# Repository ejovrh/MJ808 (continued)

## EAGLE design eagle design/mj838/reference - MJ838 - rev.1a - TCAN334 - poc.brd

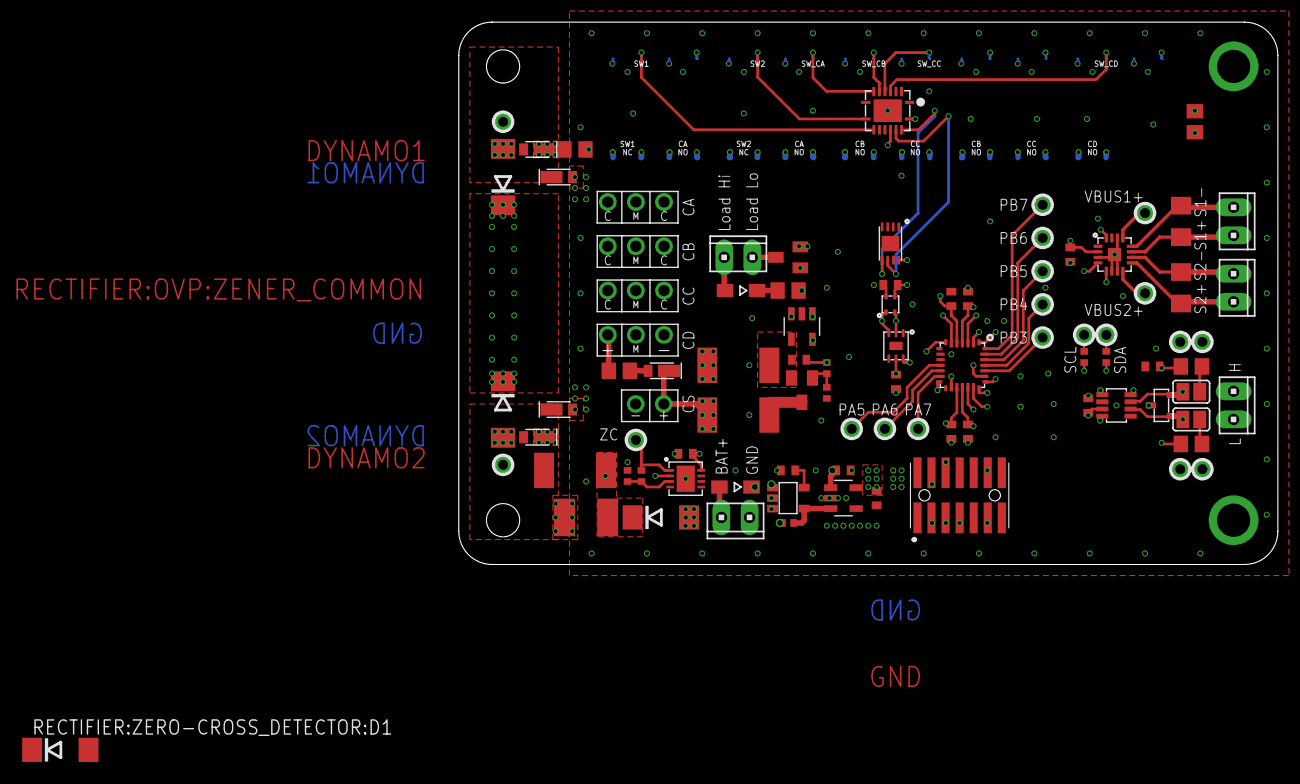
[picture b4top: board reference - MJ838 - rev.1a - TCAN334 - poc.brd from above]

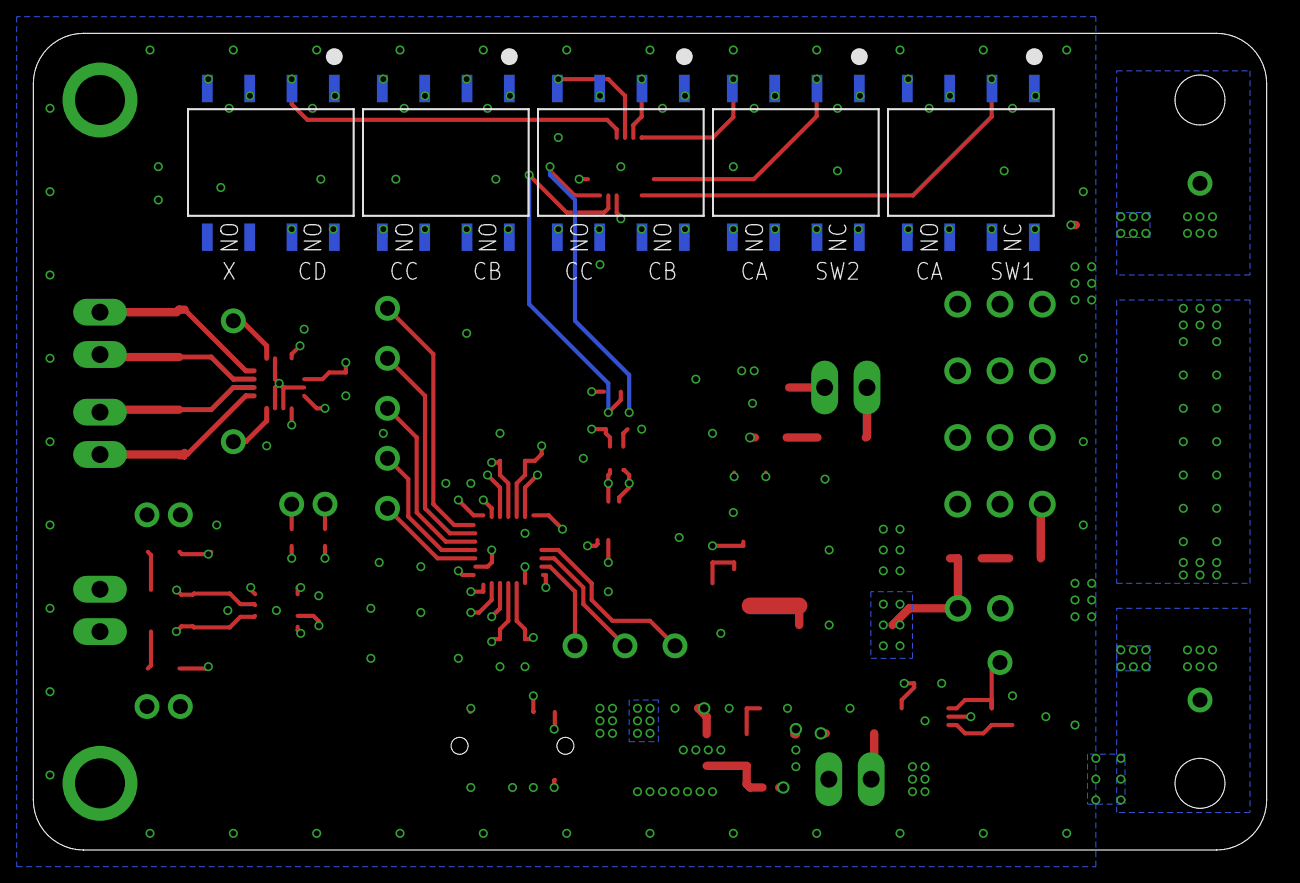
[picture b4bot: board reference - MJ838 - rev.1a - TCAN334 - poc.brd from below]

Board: 4 copper layers, 74.0 x 49.0 mm, 95 parts (5 on the bottom side), 68 nets.

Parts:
APP_LOAD:J3: Application; 10X02MTA
APP_LOAD:Q2: IRLML2402TRPBF; SOT23
C301, C305, C307, C405, C605, C801, C905: 0.1uF / 10V; C0402
C304: 1uF / 10V; C0402
C401: 47nF / 10V; C0402
C802: 0; C0402
D501, D502: BAT 60A E6327; SOD323-W
IC302: STM32F042G6U6; UFQFPN-28
IC401: TCAN334GDCNT; SOT23-8
IC402: SZNUP2105LT1G; SOT-23-3
IC602: PAC1952T-2E/4MX; VQFN16
IC701: MB85RC16PN-G-AMERE1; SON-8
IC801: DAC121C081CISD/NOPB; WSON-6
IC802: AD8515ARTZ-REEL7; SOT-23-5
IC901: SHT40-AD1F-R2; SMD
J1: Battery; 10X02MTA
J2: FTSH-107-01-L-DV-K-A; FTSH10701LDVKA
J3: CAN; 10X02MTA
J4: sense 1; 10X02MTA
J5: sense 2; 10X02MTA
Q802: IRLML2402TRPBF; SOT23
R1, R2: 4k7; R0402
R401, R402: 60R, 0.5W; R0805
R502, R504: 0R; R0805
R601, R602: 0.1R / 0.5W / 0.25%; R1206
R801: 12R/3W+++; R2512
R802: 0.1R / 1W; R2512
R803, R804: 0R; R0402
RECTIFIER:3V3:C1, RECTIFIER:3V3:C2, RECTIFIER:3V3:C7: 1uF / 10V; C0402
RECTIFIER:3V3:IC1: R3119N058A; SOT23-5
RECTIFIER:3V3:IC2: LDK320AM33R; SOT-23-5L
RECTIFIER:3V3:R1: 100k / 0.1W; R0402
RECTIFIER:GRAETZ+DELON:D1, RECTIFIER:GRAETZ+DELON:D2, RECTIFIER:GRAETZ+DELON:D3, RECTIFIER:GRAETZ+DELON:D4: CUHS20S30,H3F; US2H
RECTIFIER:GRAETZ+DELON:DELON:C1: 330μF / 35V / ultralow ESR; TH-2S
RECTIFIER:GRAETZ+DELON:DELON:SSR_NO/NO3:IC1: LAA710S; SMD_DIP8
RECTIFIER:GRAETZ+DELON:IC1: TLC59208FIRGYR; VQFN16
RECTIFIER:GRAETZ+DELON:R1: 430R/0.5W; R0805
RECTIFIER:GRAETZ+DELON:TUNING_CAPS:C2, RECTIFIER:GRAETZ+DELON:TUNING_CAPS:C3, RECTIFIER:GRAETZ+DELON:TUNING_CAPS:C4: 1500μF / 35V / ultralow ESR; TH-2S-BACK-TO-BACK
RECTIFIER:GRAETZ+DELON:TUNING_CAPS:R2: 47k; R0805
RECTIFIER:GRAETZ+DELON:TUNING_CAPS:SSR_NC/NO1:IC2, RECTIFIER:GRAETZ+DELON:TUNING_CAPS:SSR_NC/NO2:IC2: LBA710S; SMD_DIP8
RECTIFIER:GRAETZ+DELON:TUNING_CAPS:SSR_NO/NO1:IC1, RECTIFIER:GRAETZ+DELON:TUNING_CAPS:SSR_NO/NO2:IC1: LAA710S; SMD_DIP8
RECTIFIER:OVP:D1, RECTIFIER:OVP:D2: 19V/5W; DO214AA
RECTIFIER:SMOOTHING_CAP:C5: 2P 4700μF / 35V / ultralow ESR; TH
RECTIFIER:SMOOTHING_CAP:D8: CUHS20S30,H3F; US2H
RECTIFIER:ZERO-CROSS_DETECTOR:C3: 0.1uF / 10V; C0402
RECTIFIER:ZERO-CROSS_DETECTOR:C8: 10nF / 100v; C1812
RECTIFIER:ZERO-CROSS_DETECTOR:D1, RECTIFIER:ZERO-CROSS_DETECTOR:D10: 6V/3W; DO214AA
RECTIFIER:ZERO-CROSS_DETECTOR:IC1: LT1638IDD#PBF; DFN-8
RECTIFIER:ZERO-CROSS_DETECTOR:R1: 10k/3W; R2512
RECTIFIER:ZERO-CROSS_DETECTOR:R2, RECTIFIER:ZERO-CROSS_DETECTOR:R7: 10k; R0402
SJ401: CAN H term.; SJ
SJ402: CAN L term.; SJ
TP2, TP3, TP4, TP5, TP6, TP7, TP8, TP10, TP11, TP12, TP16, TP17, TP22, TP23, TP24, TP25: CAN high; TH-0.9
TP18, TP19: CAN low; TH-0.9
TP31: BAT+; TH-0.9

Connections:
3V3: C301.2, C304.2, C305.2, C405.1, C605.1, C801.2, C905.1, IC302.5_VDDA, IC302.17_VDD, IC302.18_VDDIO2, IC401.P$3, IC602.2, IC701.P$8, IC801.5, IC802.5, IC901.VDD, J2.3, R1.2, R2.2, RECTIFIER:3V3:C7.2, RECTIFIER:3V3:IC2.OUT, RECTIFIER:GRAETZ+DELON:IC1.16, RECTIFIER:GRAETZ+DELON:R1.2, RECTIFIER:ZERO-CROSS_DETECTOR:C3.2, RECTIFIER:ZERO-CROSS_DETECTOR:IC1.8_V+
12R_OHMIC_LOAD:DAC_OUT: IC801.6, IC802.3
12R_OHMIC_LOAD:GATE1: Q802.1, R803.2, R804.1
12R_OHMIC_LOAD:LOAD_LOW: Q802.3, R801.1
12R_OHMIC_LOAD:OPAMP_OUT: C802.2, IC802.1, R803.1
12R_OHMIC_LOAD:VSENSE: C802.1, IC802.4, Q802.2, R802.2
!APP_LOAD!: APP_LOAD:Q2.1, IC302.7_PA1
!LED_RST!: IC302.6_PA0, RECTIFIER:GRAETZ+DELON:IC1.13
!STBY!: IC302.23_PA15, IC401.P$8
APP_LOAD:LOAD_LOW: APP_LOAD:J3.1, APP_LOAD:Q2.3
BAT+: D501.A, J1.1
CAN_H: IC401.P$7, IC402.2, J3.2, SJ401.1, TP16.P$1, TP17.P$1
CAN_INFRA:H: R402.2, SJ401.2
CAN_INFRA:L: R401.1, SJ402.2
CAN_INFRA:SPLIT: C401.1, R401.2, R402.1
CAN_L: IC401.P$6, IC402.1, J3.1, SJ402.1, TP18.P$1, TP19.P$1
CAN_RX: IC302.19_PA9-[PA11], IC401.P$4
CAN_TX: IC302.20_PA10-[PA12], IC401.P$1
DYNAMO1: RECTIFIER:GRAETZ+DELON:D1.C, RECTIFIER:GRAETZ+DELON:D2.A, RECTIFIER:GRAETZ+DELON:TUNING_CAPS:SSR_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.6_DRAIN2-2, RECTIFIER:GRAETZ+DELON:TUNING_CAPS:SSR_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.8_DRAIN1-2, RECTIFIER:GRAETZ+DELON:TUNING_CAPS:SSR_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.6_DRAIN2-2, RECTIFIER:GRAETZ+DELON:TUNING_CAPS:SSR_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.8_DRAIN1-2, RECTIFIER:OVP:D1.A, TP2.P$1
DYNAMO2: RECTIFIER:GRAETZ+DELON:D3.C, RECTIFIER:GRAETZ+DELON:D4.A, RECTIFIER:GRAETZ+DELON:TUNING_CAPS:SSR_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.7_DRAIN1-1, RECTIFIER:OVP:D2.A, RECTIFIER:ZERO-CROSS_DETECTOR:R1.1, TP3.P$1
GND: APP_LOAD:Q2.2, C301.1, C304.1, C305.1, C307.1, C401.2, C405.2, C605.2, C801.1, C905.2, IC302.16_VSS, IC401.P$2, IC402.3, IC602.3, IC602.6, IC602.7, IC602.14, IC602.17, IC701.P$1, IC701.P$2, IC701.P$3, IC701.P$4, IC701.P$9, IC801.1, IC801.4, IC801.7, IC802.2, IC901.VSS, J1.2, J2.5, J2.7, J2.11, R802.1, R804.2, RECTIFIER:3V3:C1.2, RECTIFIER:3V3:C2.2, RECTIFIER:3V3:C7.1, RECTIFIER:3V3:IC1.2_GND, RECTIFIER:3V3:IC1.3_GND, RECTIFIER:3V3:IC2.GND, RECTIFIER:GRAETZ+DELON:D2.C, RECTIFIER:GRAETZ+DELON:D4.C, RECTIFIER:GRAETZ+DELON:DELON:C1.3_NEG, RECTIFIER:GRAETZ+DELON:IC1.1, RECTIFIER:GRAETZ+DELON:IC1.2, RECTIFIER:GRAETZ+DELON:IC1.3, RECTIFIER:GRAETZ+DELON:IC1.8, RECTIFIER:GRAETZ+DELON:IC1.17, RECTIFIER:SMOOTHING_CAP:C5.NEG, RECTIFIER:ZERO-CROSS_DETECTOR:C3.1, RECTIFIER:ZERO-CROSS_DETECTOR:C8.1, RECTIFIER:ZERO-CROSS_DETECTOR:D10.A, RECTIFIER:ZERO-CROSS_DETECTOR:IC1.4_V-, RECTIFIER:ZERO-CROSS_DETECTOR:IC1.9_V-, RECTIFIER:ZERO-CROSS_DETECTOR:R2.1
I2C_SCL: IC302.3_PF1, IC602.4, IC701.P$6, IC801.2, IC901.SCL, R1.1, RECTIFIER:GRAETZ+DELON:IC1.14, TP22.P$1
I2C_SDA: IC302.2_PF0, IC602.5, IC701.P$5, IC801.3, IC901.SDA, R2.1, RECTIFIER:GRAETZ+DELON:IC1.15, TP23.P$1
PA5: IC302.11_PA5, TP12.P$1
PA6: IC302.12_PA6, TP11.P$1
PA7: IC302.13_PA7, TP10.P$1
PB3: IC302.24_PB3, TP4.P$1
PB4: IC302.25_PB4, TP5.P$1
PB5: IC302.26_PB5, TP6.P$1
PB6: IC302.27_PB6, TP7.P$1
PB7: IC302.28_PB7, TP8.P$1
PM_!PWRDN!: IC302.1_PB8, IC602.16
RECTIFIER:3V3:!EN!: RECTIFIER:3V3:IC1.4_DOUT, RECTIFIER:3V3:IC2.EN, RECTIFIER:3V3:R1.2
RECTIFIER:3V3:CD: RECTIFIER:3V3:C1.1, RECTIFIER:3V3:IC1.5_CD
RECTIFIER:GRAETZ+DELON:!SW1!: RECTIFIER:GRAETZ+DELON:IC1.10, RECTIFIER:GRAETZ+DELON:TUNING_CAPS:SSR_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.2_CATHODE1
RECTIFIER:GRAETZ+DELON:!SW2!: RECTIFIER:GRAETZ+DELON:IC1.9, RECTIFIER:GRAETZ+DELON:TUNING_CAPS:SSR_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.2_CATHODE1
RECTIFIER:GRAETZ+DELON:!SW_CA!: RECTIFIER:GRAETZ+DELON:IC1.7, RECTIFIER:GRAETZ+DELON:TUNING_CAPS:SSR_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.4_CATHODE2, RECTIFIER:GRAETZ+DELON:TUNING_CAPS:SSR_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.4_CATHODE2
RECTIFIER:GRAETZ+DELON:!SW_CB!: RECTIFIER:GRAETZ+DELON:IC1.6, RECTIFIER:GRAETZ+DELON:TUNING_CAPS:SSR_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.2_CATHODE1, RECTIFIER:GRAETZ+DELON:TUNING_CAPS:SSR_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.2_CATHODE1
RECTIFIER:GRAETZ+DELON:!SW_CC!: RECTIFIER:GRAETZ+DELON:IC1.5, RECTIFIER:GRAETZ+DELON:TUNING_CAPS:SSR_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.4_CATHODE2, RECTIFIER:GRAETZ+DELON:TUNING_CAPS:SSR_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.4_CATHODE2
RECTIFIER:GRAETZ+DELON:!SW_CD!: RECTIFIER:GRAETZ+DELON:DELON:SSR_NO/NO3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.2_CATHODE1, RECTIFIER:GRAETZ+DELON:IC1.4
RECTIFIER:GRAETZ+DELON:DELON: RECTIFIER:GRAETZ+DELON:DELON:SSR_NO/NO3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.8_DRAIN1-2, RECTIFIER:GRAETZ+DELON:TUNING_CAPS:SSR_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.7_DRAIN1-1, RECTIFIER:GRAETZ+DELON:TUNING_CAPS:SSR_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.6_DRAIN2-2, RECTIFIER:GRAETZ+DELON:TUNING_CAPS:SSR_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.8_DRAIN1-2, RECTIFIER:GRAETZ+DELON:TUNING_CAPS:SSR_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.6_DRAIN2-2, RECTIFIER:GRAETZ+DELON:TUNING_CAPS:SSR_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.8_DRAIN1-2
RECTIFIER:GRAETZ+DELON:DELON:SW1_OUT: RECTIFIER:GRAETZ+DELON:DELON:C1.2_MID, RECTIFIER:GRAETZ+DELON:DELON:SSR_NO/NO3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.7_DRAIN1-1
RECTIFIER:GRAETZ+DELON:SSR_ANODE: RECTIFIER:GRAETZ+DELON:DELON:SSR_NO/NO3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.1_ANODE1, RECTIFIER:GRAETZ+DELON:DELON:SSR_NO/NO3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.3_ANODE2, RECTIFIER:GRAETZ+DELON:R1.1, RECTIFIER:GRAETZ+DELON:TUNING_CAPS:SSR_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.1_ANODE1, RECTIFIER:GRAETZ+DELON:TUNING_CAPS:SSR_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.3_ANODE2, RECTIFIER:GRAETZ+DELON:TUNING_CAPS:SSR_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.1_ANODE1, RECTIFIER:GRAETZ+DELON:TUNING_CAPS:SSR_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.3_ANODE2, RECTIFIER:GRAETZ+DELON:TUNING_CAPS:SSR_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.1_ANODE1, RECTIFIER:GRAETZ+DELON:TUNING_CAPS:SSR_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.3_ANODE2, RECTIFIER:GRAETZ+DELON:TUNING_CAPS:SSR_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.1_ANODE1, RECTIFIER:GRAETZ+DELON:TUNING_CAPS:SSR_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.3_ANODE2
RECTIFIER:GRAETZ+DELON:TUNING_CAPS:CAA: RECTIFIER:GRAETZ+DELON:TUNING_CAPS:C2.1_C, RECTIFIER:GRAETZ+DELON:TUNING_CAPS:SSR_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.5_DRAIN2-1
RECTIFIER:GRAETZ+DELON:TUNING_CAPS:CAB: RECTIFIER:GRAETZ+DELON:TUNING_CAPS:C2.3_C, RECTIFIER:GRAETZ+DELON:TUNING_CAPS:SSR_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.5_DRAIN2-1
RECTIFIER:GRAETZ+DELON:TUNING_CAPS:CBA: RECTIFIER:GRAETZ+DELON:TUNING_CAPS:C3.1_C, RECTIFIER:GRAETZ+DELON:TUNING_CAPS:SSR_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.7_DRAIN1-1
RECTIFIER:GRAETZ+DELON:TUNING_CAPS:CBB: RECTIFIER:GRAETZ+DELON:TUNING_CAPS:C3.3_C, RECTIFIER:GRAETZ+DELON:TUNING_CAPS:SSR_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.7_DRAIN1-1
RECTIFIER:GRAETZ+DELON:TUNING_CAPS:CCA: RECTIFIER:GRAETZ+DELON:TUNING_CAPS:C4.1_C, RECTIFIER:GRAETZ+DELON:TUNING_CAPS:SSR_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.5_DRAIN2-1
RECTIFIER:GRAETZ+DELON:TUNING_CAPS:CCB: RECTIFIER:GRAETZ+DELON:TUNING_CAPS:C4.3_C, RECTIFIER:GRAETZ+DELON:TUNING_CAPS:SSR_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.5_DRAIN2-1
RECTIFIER:GRAETZ+DELON:TUNING_CAPS:TUNING_CAP_BIAS: RECTIFIER:GRAETZ+DELON:TUNING_CAPS:C2.2_MID, RECTIFIER:GRAETZ+DELON:TUNING_CAPS:C3.2_MID, RECTIFIER:GRAETZ+DELON:TUNING_CAPS:C4.2_MID, RECTIFIER:GRAETZ+DELON:TUNING_CAPS:R2.1
RECTIFIER:LDO_IN: D501.C, R504.2, RECTIFIER:3V3:C2.1, RECTIFIER:3V3:IC1.1_VDD, RECTIFIER:3V3:IC2.IN, RECTIFIER:3V3:R1.1
RECTIFIER:OVP:ZENER_COMMON: RECTIFIER:OVP:D1.C, RECTIFIER:OVP:D2.C
RECTIFIER:SMOOTHINGCAP_IN: R502.2, RECTIFIER:SMOOTHING_CAP:D8.C
RECTIFIER:VDC_TOWARDS_LDO: D502.C, R504.1
RECTIFIER:V_RECT_TP1-IN: R502.1, RECTIFIER:GRAETZ+DELON:D1.A, RECTIFIER:GRAETZ+DELON:D3.A, RECTIFIER:GRAETZ+DELON:DELON:C1.1_POS, RECTIFIER:GRAETZ+DELON:TUNING_CAPS:R2.2
RECTIFIER:ZERO-CROSS_DETECTOR:OPAMP_IN+: RECTIFIER:ZERO-CROSS_DETECTOR:IC1.3_A_IN+, RECTIFIER:ZERO-CROSS_DETECTOR:R2.2, RECTIFIER:ZERO-CROSS_DETECTOR:R7.2
RECTIFIER:ZERO-CROSS_DETECTOR:OPAMP_IN-: RECTIFIER:ZERO-CROSS_DETECTOR:C8.2, RECTIFIER:ZERO-CROSS_DETECTOR:D10.C, RECTIFIER:ZERO-CROSS_DETECTOR:IC1.2_A_IN-, RECTIFIER:ZERO-CROSS_DETECTOR:R1.2
SENSE1+: IC602.11, J4.1, R601.1
SENSE1-: IC602.12, J4.2, R601.2
SENSE2+: IC602.10, J5.2, R602.1
SENSE2-: IC602.9, J5.1, R602.2
SYS_NRST: C307.2, IC302.4_NRST, J2.12
SYS_SWCLK: IC302.22_PA14, J2.6
SYS_SWDIO: IC302.21_PA13, J2.4
VBUS1+: IC602.13, TP24.P$1
VBUS2+: IC602.8, TP25.P$1
VDC: APP_LOAD:J3.2, D502.A, R801.2, RECTIFIER:SMOOTHING_CAP:C5.POS, RECTIFIER:SMOOTHING_CAP:D8.A
ZEROCROSS: IC302.14_PB0, RECTIFIER:ZERO-CROSS_DETECTOR:IC1.1_A_OUT, RECTIFIER:ZERO-CROSS_DETECTOR:R7.1, TP31.P$1

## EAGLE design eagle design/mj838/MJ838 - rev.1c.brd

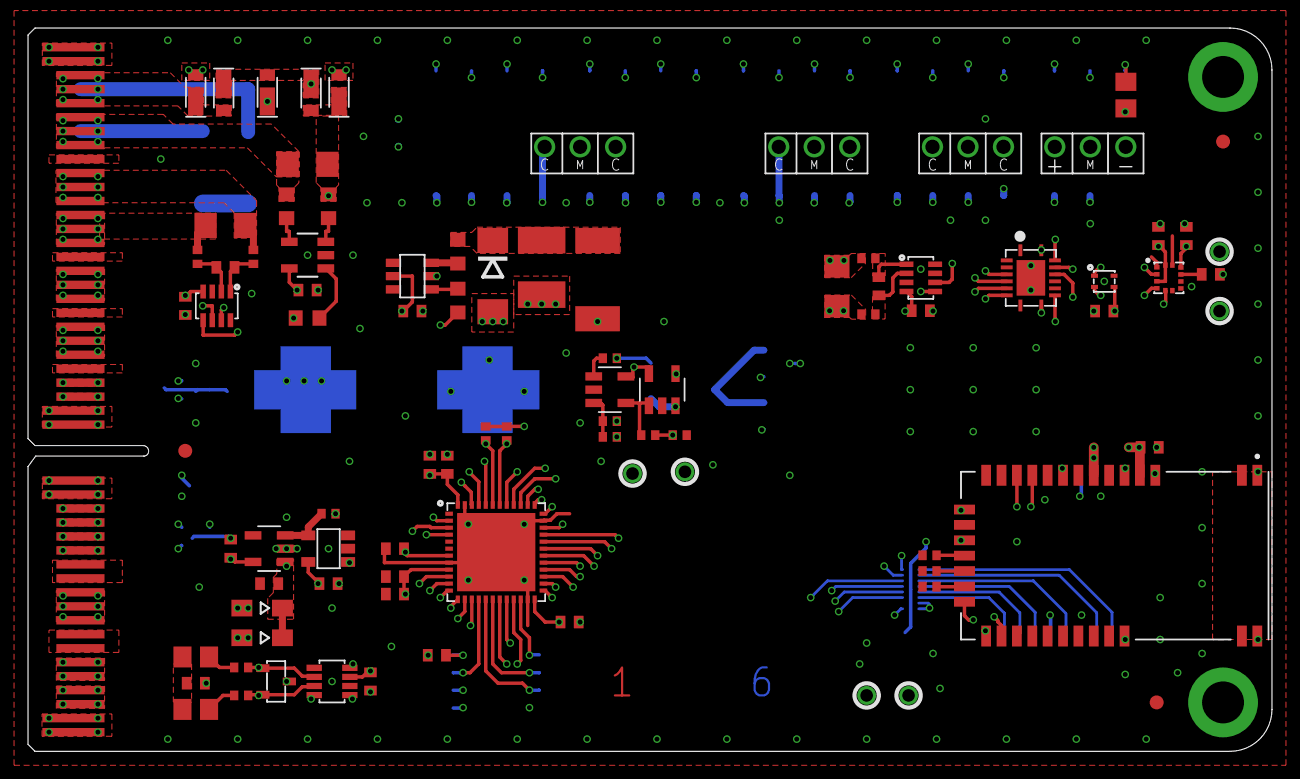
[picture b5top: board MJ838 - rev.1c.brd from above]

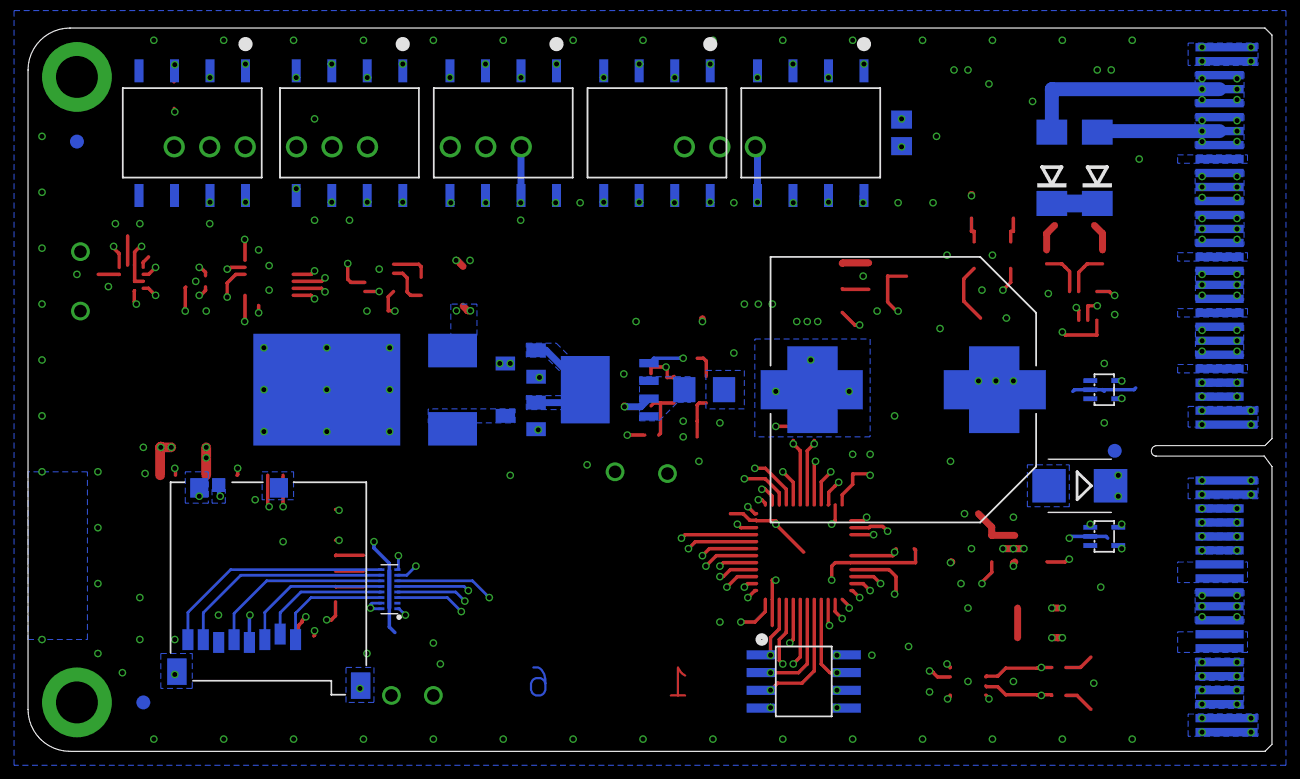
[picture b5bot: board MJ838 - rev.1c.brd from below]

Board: 6 copper layers, 89.0 x 51.8 mm, 114 parts (24 on the bottom side), 102 nets.

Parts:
ACCELEROMETER:C1: 0.1uF / 10V; C0402
ACCELEROMETER:C2: 0.2uF / 10V; C0402
ACCELEROMETER:C4: 0.11uF / 10V; C0402
ACCELEROMETER:IC1: ADXL367BCCZ-RL7; LGA-12
ADJUSTABLE_LOAD:IC2, ADJUSTABLE_LOAD:IC4: AD8515ARTZ-REEL7; SOT-23-5
ADJUSTABLE_LOAD:IC3: PH2925U,115; SOT669
ADJUSTABLE_LOAD:INA219:C1: 0.1uF / 10V; C0402
ADJUSTABLE_LOAD:INA219:C2: ???; C0402
ADJUSTABLE_LOAD:INA219:IC3: INA219BIDCNT; SOT-23-8
ADJUSTABLE_LOAD:INA219:R3, ADJUSTABLE_LOAD:INA219:R5: ???; R0402
ADJUSTABLE_LOAD:INA219:R4: 0.1R / 0.5W - LVK12R100CER; R1206
ADJUSTABLE_LOAD:Q2, ADJUSTABLE_LOAD:Q3: BSS123; SOT23
ADJUSTABLE_LOAD:R1: 3k; R0402
ADJUSTABLE_LOAD:R2: 0.1R / 0.5W - LVK12R100CER; R1206
ADJUSTABLE_LOAD:R3: 1k; R0402
ADJUSTABLE_LOAD:R4: 27k; R0402
ADJUSTABLE_LOAD:R5: 12R, 20W, AP725 12R F; TO-263-2
ADJUSTABLE_LOAD:R6: 100k; R0402
ADJUSTABLE_LOAD:R7: 10k; R0402
BLUETOOTH:C1: 10uF / 10V; C0402
BLUETOOTH:IC1: RN4678-V/RM113; MODULE_RN4678-V/RM100
BLUETOOTH:R1, BLUETOOTH:R2, BLUETOOTH:R3: 0R; R0402
CAN_INFRA:C1: 47nF / 10V; C0402
CAN_INFRA:C5: 0.1uF / 10V; C0402
CAN_INFRA:IC1: TCAN334GDCNT; SOT23-8
CAN_INFRA:IC2: SZNUP2105LT1G; SOT-23-3
CAN_INFRA:R1, CAN_INFRA:R2: 60R, 0.5W; R0805
CAN_INFRA:R3, CAN_INFRA:R4: 0; R0402
CONN1: MEC1-150-02-F-D-RA1-SL; SMD
D1: SMLVT3V3; SMB
FID1, FID2, FID3, FID4, FID5, FID6: n/a; FIDUCIAL_1MM
HUMIDITY_SENSOR:C5: 0.1uF / 10V; C0402
HUMIDITY_SENSOR:IC1: SHT40-AD1F-R2; SMD
IC1, IC2: ESDALC6V1W5; SOT323-5
INA1:C1: 0.1uF / 10V; C0402
INA1:C2: ???; C0402
INA1:IC3: INA219BIDCNT; SOT-23-8
INA1:R3, INA1:R5: ???; R0402
INA1:R4: 0.1R / 0.5W - LVK12R100CER; R1206
M-RAM:C2: 0.1uF / 10V; C0402
M-RAM:IC1: S3A3204V0M-AI1AT; SOIC08
MARKER1: 6 layer; 6L
RECTIFIER:3V3:C1, RECTIFIER:3V3:C2, RECTIFIER:3V3:C7: 1uF / 10V; C0402
RECTIFIER:3V3:IC1: R3119N058A; SOT23-5
RECTIFIER:3V3:IC2: LDK320AM33R; SOT-23-5L
RECTIFIER:3V3:R1: 100k / 0.1W; R0402
RECTIFIER:D1, RECTIFIER:D2: BAT 60A E6327; SOD323-W
RECTIFIER:DYNAMO_OVP:D3, RECTIFIER:DYNAMO_OVP:D4: 19V/5W; DO214AA
RECTIFIER:GRAETZ+DELON:D1, RECTIFIER:GRAETZ+DELON:D2, RECTIFIER:GRAETZ+DELON:D3, RECTIFIER:GRAETZ+DELON:D4: CUHS20S30,H3F; US2H
RECTIFIER:GRAETZ+DELON:DELON:C1: 330μF / 35V / ultralow ESR; TH-2S
RECTIFIER:GRAETZ+DELON:DELON:SSR_NO/NO3:IC1: LAA710S; SMD_DIP8
RECTIFIER:GRAETZ+DELON:IC1: TLC59208FIRGYR; VQFN16
RECTIFIER:GRAETZ+DELON:R1: 625; R0805
RECTIFIER:GRAETZ+DELON:TUNING_CAPS:C2, RECTIFIER:GRAETZ+DELON:TUNING_CAPS:C3, RECTIFIER:GRAETZ+DELON:TUNING_CAPS:C4: 1500μF / 35V / ultralow ESR; TH-2S-BACK-TO-BACK
RECTIFIER:GRAETZ+DELON:TUNING_CAPS:R2: 47k; R0805
RECTIFIER:GRAETZ+DELON:TUNING_CAPS:SSR_NO/NO1:IC1, RECTIFIER:GRAETZ+DELON:TUNING_CAPS:SSR_NO/NO2:IC1, RECTIFIER:GRAETZ+DELON:TUNING_CAPS:SSR_NO/NO3:IC1, RECTIFIER:GRAETZ+DELON:TUNING_CAPS:SSR_NO/NO4:IC1: LAA710S; SMD_DIP8
RECTIFIER:PHASE_SHIFT:C1: 0.1uF / 10V; C0402
RECTIFIER:PHASE_SHIFT:IC1: LT1716CS5#TRMPBF; SOT23-5
RECTIFIER:PHASE_SHIFT:R1, RECTIFIER:PHASE_SHIFT:R2, RECTIFIER:PHASE_SHIFT:R3: 0R; R0603
RECTIFIER:PHASE_SHIFT:R4: 0.01R / 0.5W / 0.25%; R1206
RECTIFIER:SMOOTHING_CAP:C1: EEE-FK1E472SV; CAP_EEEFK1E472SV
RECTIFIER:SMOOTHING_CAP:D8: CUHS20S30,H3F; US2H
RECTIFIER:ZERO-CROSS_DETECTOR:C3: 0.1uF / 10V; C0402
RECTIFIER:ZERO-CROSS_DETECTOR:C8: 10nF / 100v; C1812
RECTIFIER:ZERO-CROSS_DETECTOR:D1: 6V/3W; DO214AA
RECTIFIER:ZERO-CROSS_DETECTOR:IC1: TLV6703DDCR; SOT-23
RECTIFIER:ZERO-CROSS_DETECTOR:R1: 10k/3W; R2512
RECTIFIER:ZERO-CROSS_DETECTOR:R2, RECTIFIER:ZERO-CROSS_DETECTOR:R3: 0R; R0603
SD_CARD:IC1: 0473521001; SMD
SD_CARD:IC3: EMIF06-MSD02N16; MICRO_QFN
STM32L4:C1, STM32L4:C2, STM32L4:C4, STM32L4:C8: 0.1uF / 10V; C0402
STM32L4:C3: 4.7uF / 10V; C0402
STM32L4:C6: 1uF / 10V; C0402
STM32L4:IC1: STM32L4P5CGU6; UFQFPN48
STM32L4:R1, STM32L4:R2: 1k; R0402
TP1, TP2, TP3, TP4, TP5, TP6: CAN high; TH-0.9

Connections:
3V3: ACCELEROMETER:C1.2, ACCELEROMETER:C4.2, ACCELEROMETER:IC1.3_MISO/ASEL, ACCELEROMETER:IC1.10_VS, ACCELEROMETER:IC1.12_VDDIO, ADJUSTABLE_LOAD:IC2.5, ADJUSTABLE_LOAD:IC4.5, ADJUSTABLE_LOAD:INA219:C1.1, ADJUSTABLE_LOAD:INA219:IC3.P$4, ADJUSTABLE_LOAD:R6.2, BLUETOOTH:C1.2, BLUETOOTH:IC1.4, BLUETOOTH:IC1.7, CAN_INFRA:C5.1, CAN_INFRA:IC1.P$3, CONN1.33, CONN1.34, D1.C, HUMIDITY_SENSOR:C5.1, HUMIDITY_SENSOR:IC1.VDD, INA1:C1.1, INA1:IC3.P$4, INA1:IC3.P$7, M-RAM:C2.2, M-RAM:IC1.8, RECTIFIER:3V3:C7.2, RECTIFIER:3V3:IC2.OUT, RECTIFIER:GRAETZ+DELON:IC1.16, RECTIFIER:GRAETZ+DELON:R1.2, RECTIFIER:PHASE_SHIFT:C1.2, RECTIFIER:PHASE_SHIFT:IC1.5, RECTIFIER:ZERO-CROSS_DETECTOR:C3.2, RECTIFIER:ZERO-CROSS_DETECTOR:IC1.P$5, SD_CARD:IC1.VDD, SD_CARD:IC3.15, SD_CARD:IC3.16, STM32L4:C1.2, STM32L4:C2.2, STM32L4:C3.2, STM32L4:C6.2, STM32L4:C8.2, STM32L4:IC1.P$9, STM32L4:IC1.P$24, STM32L4:IC1.P$48, STM32L4:R1.2, STM32L4:R2.2
!LED_RST!: RECTIFIER:GRAETZ+DELON:IC1.13, STM32L4:IC1.P$44
!QSPI_CS!: M-RAM:IC1.1, STM32L4:IC1.P$22
!RN4678_SWBTN!: BLUETOOTH:IC1.5, STM32L4:IC1.P$2
!STBY!: CAN_INFRA:IC1.P$8, STM32L4:IC1.P$13
ACCELEROMETER:VREG: ACCELEROMETER:C2.2, ACCELEROMETER:IC1.9_VREG_OUT
ADJL: ADJUSTABLE_LOAD:Q2.1, STM32L4:IC1.P$38
ADJUSTABLE_LOAD:DRAIN: ADJUSTABLE_LOAD:IC3.D, ADJUSTABLE_LOAD:Q2.2, ADJUSTABLE_LOAD:Q3.2
ADJUSTABLE_LOAD:GATE_COMMON: ADJUSTABLE_LOAD:IC3.G, ADJUSTABLE_LOAD:R3.2
ADJUSTABLE_LOAD:GATE_COMMON-DRIVER_OUT: ADJUSTABLE_LOAD:IC2.1, ADJUSTABLE_LOAD:R3.1
ADJUSTABLE_LOAD:IN+: ADJUSTABLE_LOAD:IC2.3, ADJUSTABLE_LOAD:R6.1, ADJUSTABLE_LOAD:R7.2
ADJUSTABLE_LOAD:IN-: ADJUSTABLE_LOAD:INA219:R3.2, ADJUSTABLE_LOAD:INA219:R4.2, ADJUSTABLE_LOAD:R5.2
ADJUSTABLE_LOAD:INA219:IN+L: ADJUSTABLE_LOAD:INA219:C2.1, ADJUSTABLE_LOAD:INA219:IC3.P$1, ADJUSTABLE_LOAD:INA219:R5.1
ADJUSTABLE_LOAD:INA219:IN-H: ADJUSTABLE_LOAD:INA219:C2.2, ADJUSTABLE_LOAD:INA219:IC3.P$2, ADJUSTABLE_LOAD:INA219:R3.1
ADJUSTABLE_LOAD:LOAD_LOW: ADJUSTABLE_LOAD:Q2.3, ADJUSTABLE_LOAD:R5.1
ADJUSTABLE_LOAD:SENSE_AMP_IN-: ADJUSTABLE_LOAD:IC4.4, ADJUSTABLE_LOAD:R1.2, ADJUSTABLE_LOAD:R4.1
ADJUSTABLE_LOAD:VSENSE: ADJUSTABLE_LOAD:IC3.S1, ADJUSTABLE_LOAD:IC3.S2, ADJUSTABLE_LOAD:IC3.S3, ADJUSTABLE_LOAD:IC4.3, ADJUSTABLE_LOAD:R2.2
ADJUSTABLE_LOAD:VSENSE-AMP_OUT: ADJUSTABLE_LOAD:IC2.4, ADJUSTABLE_LOAD:IC4.1, ADJUSTABLE_LOAD:R4.2
ADXL_INT1: ACCELEROMETER:IC1.5_INT1, STM32L4:IC1.P$15
APPL: ADJUSTABLE_LOAD:Q3.1, STM32L4:IC1.P$29
APP_LOW: ADJUSTABLE_LOAD:Q3.3, CONN1.55, CONN1.56, CONN1.57, CONN1.58, CONN1.59, CONN1.60
BAT+: CONN1.17, CONN1.18, CONN1.19, CONN1.20, CONN1.21, CONN1.22, RECTIFIER:D1.A
BLUETOOTH:EAN: BLUETOOTH:IC1.20, BLUETOOTH:R3.1
BLUETOOTH:P2_0: BLUETOOTH:IC1.18, BLUETOOTH:R1.1
BLUETOOTH:P2_4: BLUETOOTH:IC1.19, BLUETOOTH:R2.1
CAN_H: CAN_INFRA:IC1.P$7, CAN_INFRA:IC2.2, CAN_INFRA:R3.2, CONN1.5, CONN1.6, CONN1.7, CONN1.8
CAN_INFRA:H: CAN_INFRA:R2.2, CAN_INFRA:R3.1
CAN_INFRA:L: CAN_INFRA:R1.1, CAN_INFRA:R4.1
CAN_INFRA:SPLIT: CAN_INFRA:C1.1, CAN_INFRA:R1.2, CAN_INFRA:R2.1
CAN_L: CAN_INFRA:IC1.P$6, CAN_INFRA:IC2.1, CAN_INFRA:R4.2, CONN1.9, CONN1.10, CONN1.11, CONN1.12
DAC: ADJUSTABLE_LOAD:R7.1, STM32L4:IC1.P$14, TP6.P$1
DYNAMO1: CONN1.91, CONN1.92, CONN1.93, CONN1.94, CONN1.95, CONN1.96, RECTIFIER:DYNAMO_OVP:D4.A, RECTIFIER:GRAETZ+DELON:D1.C, RECTIFIER:GRAETZ+DELON:D2.A, RECTIFIER:GRAETZ+DELON:TUNING_CAPS:SSR_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.6_DRAIN2-2, RECTIFIER:GRAETZ+DELON:TUNING_CAPS:SSR_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.8_DRAIN1-2, RECTIFIER:GRAETZ+DELON:TUNING_CAPS:SSR_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.6_DRAIN2-2, RECTIFIER:GRAETZ+DELON:TUNING_CAPS:SSR_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.8_DRAIN1-2, RECTIFIER:ZERO-CROSS_DETECTOR:R1.1
DYNAMO2: CONN1.85, CONN1.86, CONN1.87, CONN1.88, CONN1.89, CONN1.90, RECTIFIER:DYNAMO_OVP:D3.A, RECTIFIER:PHASE_SHIFT:R3.1, RECTIFIER:PHASE_SHIFT:R4.1
GND: ACCELEROMETER:C1.1, ACCELEROMETER:C2.1, ACCELEROMETER:C4.1, ACCELEROMETER:IC1.1_SCLK, ACCELEROMETER:IC1.7_GND, ACCELEROMETER:IC1.8_ADC_IN, ACCELEROMETER:IC1.11_GND, ADJUSTABLE_LOAD:IC2.2, ADJUSTABLE_LOAD:IC4.2, ADJUSTABLE_LOAD:INA219:C1.2, ADJUSTABLE_LOAD:INA219:IC3.P$3, ADJUSTABLE_LOAD:INA219:IC3.P$7, ADJUSTABLE_LOAD:INA219:IC3.P$8, ADJUSTABLE_LOAD:R1.1, ADJUSTABLE_LOAD:R2.1, ADJUSTABLE_LOAD:R5.DIE, BLUETOOTH:C1.1, BLUETOOTH:IC1.1, BLUETOOTH:IC1.2, BLUETOOTH:IC1.3, BLUETOOTH:IC1.31, BLUETOOTH:IC1.32, BLUETOOTH:IC1.33, BLUETOOTH:R1.2, BLUETOOTH:R2.2, BLUETOOTH:R3.2, CAN_INFRA:C1.2, CAN_INFRA:C5.2, CAN_INFRA:IC1.P$2, CAN_INFRA:IC2.3, CONN1.1, CONN1.2, CONN1.3, CONN1.4, CONN1.13, CONN1.14, CONN1.15, CONN1.16, CONN1.23, CONN1.24, CONN1.25, CONN1.26, CONN1.35, CONN1.36, CONN1.37, CONN1.38, CONN1.45, CONN1.46, CONN1.47, CONN1.48, CONN1.53, CONN1.54, CONN1.61, CONN1.62, CONN1.69, CONN1.70, CONN1.83, CONN1.84, CONN1.97, CONN1.98, CONN1.99, CONN1.100, D1.A, HUMIDITY_SENSOR:C5.2, HUMIDITY_SENSOR:IC1.VSS, IC1.GND, IC2.GND, INA1:C1.2, INA1:IC3.P$3, INA1:IC3.P$8, M-RAM:C2.1, M-RAM:IC1.4, RECTIFIER:3V3:C1.2, RECTIFIER:3V3:C2.2, RECTIFIER:3V3:C7.1, RECTIFIER:3V3:IC1.2_GND, RECTIFIER:3V3:IC1.3_GND, RECTIFIER:3V3:IC2.GND, RECTIFIER:GRAETZ+DELON:D2.C, RECTIFIER:GRAETZ+DELON:D4.C, RECTIFIER:GRAETZ+DELON:DELON:C1.3_NEG, RECTIFIER:GRAETZ+DELON:IC1.1, RECTIFIER:GRAETZ+DELON:IC1.2, RECTIFIER:GRAETZ+DELON:IC1.3, RECTIFIER:GRAETZ+DELON:IC1.8, RECTIFIER:GRAETZ+DELON:IC1.17, RECTIFIER:PHASE_SHIFT:C1.1, RECTIFIER:PHASE_SHIFT:IC1.2, RECTIFIER:SMOOTHING_CAP:C1.-, RECTIFIER:ZERO-CROSS_DETECTOR:C3.1, RECTIFIER:ZERO-CROSS_DETECTOR:C8.1, RECTIFIER:ZERO-CROSS_DETECTOR:D1.A, RECTIFIER:ZERO-CROSS_DETECTOR:IC1.P$2, RECTIFIER:ZERO-CROSS_DETECTOR:IC1.P$4, RECTIFIER:ZERO-CROSS_DETECTOR:IC1.P$6, SD_CARD:IC1.GND, SD_CARD:IC1.S1, SD_CARD:IC1.S2, SD_CARD:IC1.S3, SD_CARD:IC1.S4, SD_CARD:IC3.17, STM32L4:C1.1, STM32L4:C2.1, STM32L4:C3.1, STM32L4:C4.1, STM32L4:C6.1, STM32L4:C8.1, STM32L4:IC1.P$8, STM32L4:IC1.P$23, STM32L4:IC1.P$35, STM32L4:IC1.P$47, STM32L4:IC1.PAD
I2C_SCL: ACCELEROMETER:IC1.4_!CS!/SCL, ADJUSTABLE_LOAD:INA219:IC3.P$5, HUMIDITY_SENSOR:IC1.SCL, INA1:IC3.P$5, RECTIFIER:GRAETZ+DELON:IC1.14, STM32L4:IC1.P$42, STM32L4:R2.1, TP1.P$1
I2C_SDA: ACCELEROMETER:IC1.2_MOSI/SDA, ADJUSTABLE_LOAD:INA219:IC3.P$6, HUMIDITY_SENSOR:IC1.SDA, INA1:IC3.P$6, RECTIFIER:GRAETZ+DELON:IC1.15, STM32L4:IC1.P$43, STM32L4:R1.1, TP2.P$1
INA1:IN+L: INA1:C2.1, INA1:IC3.P$1, INA1:R5.1
INA1:IN-H: INA1:C2.2, INA1:IC3.P$2, INA1:R3.1
MJ8X8_8V4_H: CONN1.77, CONN1.78, CONN1.79, CONN1.80, CONN1.81, CONN1.82, INA1:R4.1, INA1:R5.2
MJ8X8_8V4_L: CONN1.71, CONN1.72, CONN1.73, CONN1.74, CONN1.75, CONN1.76, INA1:R3.2, INA1:R4.2
PHASE: CONN1.51, CONN1.52, IC1.I4, RECTIFIER:PHASE_SHIFT:R1.2, STM32L4:IC1.P$12
QSPI_CLK: M-RAM:IC1.6, STM32L4:IC1.P$21
QSPI_IO0: M-RAM:IC1.5, STM32L4:IC1.P$19
QSPI_IO1: M-RAM:IC1.2, STM32L4:IC1.P$18
QSPI_IO2: M-RAM:IC1.3, STM32L4:IC1.P$17
QSPI_IO3: M-RAM:IC1.7, STM32L4:IC1.P$16
RECTIFIER:3V3:!EN!: RECTIFIER:3V3:IC1.4_DOUT, RECTIFIER:3V3:IC2.EN, RECTIFIER:3V3:R1.2
RECTIFIER:3V3:CD: RECTIFIER:3V3:C1.1, RECTIFIER:3V3:IC1.5_CD
RECTIFIER:AC: RECTIFIER:GRAETZ+DELON:D3.C, RECTIFIER:GRAETZ+DELON:D4.A, RECTIFIER:GRAETZ+DELON:TUNING_CAPS:SSR_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.7_DRAIN1-1, RECTIFIER:PHASE_SHIFT:R2.1, RECTIFIER:PHASE_SHIFT:R4.2
RECTIFIER:DYNAMO_OVP:ZENER_COMMON: RECTIFIER:DYNAMO_OVP:D3.C, RECTIFIER:DYNAMO_OVP:D4.C
RECTIFIER:GRAETZ+DELON:!SW1!: RECTIFIER:GRAETZ+DELON:IC1.10, RECTIFIER:GRAETZ+DELON:TUNING_CAPS:SSR_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.2_CATHODE1
RECTIFIER:GRAETZ+DELON:!SW2!: RECTIFIER:GRAETZ+DELON:IC1.9, RECTIFIER:GRAETZ+DELON:TUNING_CAPS:SSR_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.2_CATHODE1
RECTIFIER:GRAETZ+DELON:!SW_CA!: RECTIFIER:GRAETZ+DELON:IC1.7, RECTIFIER:GRAETZ+DELON:TUNING_CAPS:SSR_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.4_CATHODE2, RECTIFIER:GRAETZ+DELON:TUNING_CAPS:SSR_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.4_CATHODE2
RECTIFIER:GRAETZ+DELON:!SW_CB!: RECTIFIER:GRAETZ+DELON:IC1.6, RECTIFIER:GRAETZ+DELON:TUNING_CAPS:SSR_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.2_CATHODE1, RECTIFIER:GRAETZ+DELON:TUNING_CAPS:SSR_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.2_CATHODE1
RECTIFIER:GRAETZ+DELON:!SW_CC!: RECTIFIER:GRAETZ+DELON:IC1.5, RECTIFIER:GRAETZ+DELON:TUNING_CAPS:SSR_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.4_CATHODE2, RECTIFIER:GRAETZ+DELON:TUNING_CAPS:SSR_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.4_CATHODE2
RECTIFIER:GRAETZ+DELON:!SW_CD!: RECTIFIER:GRAETZ+DELON:DELON:SSR_NO/NO3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.2_CATHODE1, RECTIFIER:GRAETZ+DELON:IC1.4
RECTIFIER:GRAETZ+DELON:DELON: RECTIFIER:GRAETZ+DELON:DELON:SSR_NO/NO3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.8_DRAIN1-2, RECTIFIER:GRAETZ+DELON:TUNING_CAPS:SSR_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.6_DRAIN2-2, RECTIFIER:GRAETZ+DELON:TUNING_CAPS:SSR_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.8_DRAIN1-2, RECTIFIER:GRAETZ+DELON:TUNING_CAPS:SSR_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.7_DRAIN1-1, RECTIFIER:GRAETZ+DELON:TUNING_CAPS:SSR_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.6_DRAIN2-2, RECTIFIER:GRAETZ+DELON:TUNING_CAPS:SSR_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.8_DRAIN1-2
RECTIFIER:GRAETZ+DELON:DELON:SW1_OUT: RECTIFIER:GRAETZ+DELON:DELON:C1.2_MID, RECTIFIER:GRAETZ+DELON:DELON:SSR_NO/NO3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.7_DRAIN1-1
RECTIFIER:GRAETZ+DELON:SSR_ANODE: RECTIFIER:GRAETZ+DELON:DELON:SSR_NO/NO3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.1_ANODE1, RECTIFIER:GRAETZ+DELON:DELON:SSR_NO/NO3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.3_ANODE2, RECTIFIER:GRAETZ+DELON:R1.1, RECTIFIER:GRAETZ+DELON:TUNING_CAPS:SSR_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.1_ANODE1, RECTIFIER:GRAETZ+DELON:TUNING_CAPS:SSR_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.3_ANODE2, RECTIFIER:GRAETZ+DELON:TUNING_CAPS:SSR_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.1_ANODE1, RECTIFIER:GRAETZ+DELON:TUNING_CAPS:SSR_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.3_ANODE2, RECTIFIER:GRAETZ+DELON:TUNING_CAPS:SSR_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.1_ANODE1, RECTIFIER:GRAETZ+DELON:TUNING_CAPS:SSR_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.3_ANODE2, RECTIFIER:GRAETZ+DELON:TUNING_CAPS:SSR_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.1_ANODE1, RECTIFIER:GRAETZ+DELON:TUNING_CAPS:SSR_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.3_ANODE2
RECTIFIER:GRAETZ+DELON:TUNING_CAPS:CAA: RECTIFIER:GRAETZ+DELON:TUNING_CAPS:C2.1_C, RECTIFIER:GRAETZ+DELON:TUNING_CAPS:SSR_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.5_DRAIN2-1
RECTIFIER:GRAETZ+DELON:TUNING_CAPS:CAB: RECTIFIER:GRAETZ+DELON:TUNING_CAPS:C2.3_C, RECTIFIER:GRAETZ+DELON:TUNING_CAPS:SSR_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.5_DRAIN2-1
RECTIFIER:GRAETZ+DELON:TUNING_CAPS:CBA: RECTIFIER:GRAETZ+DELON:TUNING_CAPS:C3.1_C, RECTIFIER:GRAETZ+DELON:TUNING_CAPS:SSR_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.7_DRAIN1-1
RECTIFIER:GRAETZ+DELON:TUNING_CAPS:CBB: RECTIFIER:GRAETZ+DELON:TUNING_CAPS:C3.3_C, RECTIFIER:GRAETZ+DELON:TUNING_CAPS:SSR_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.7_DRAIN1-1
RECTIFIER:GRAETZ+DELON:TUNING_CAPS:CCA: RECTIFIER:GRAETZ+DELON:TUNING_CAPS:C4.1_C, RECTIFIER:GRAETZ+DELON:TUNING_CAPS:SSR_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.5_DRAIN2-1
RECTIFIER:GRAETZ+DELON:TUNING_CAPS:CCB: RECTIFIER:GRAETZ+DELON:TUNING_CAPS:C4.3_C, RECTIFIER:GRAETZ+DELON:TUNING_CAPS:SSR_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.5_DRAIN2-1
RECTIFIER:GRAETZ+DELON:TUNING_CAPS:TUNING_CAP_BIAS: RECTIFIER:GRAETZ+DELON:TUNING_CAPS:C2.2_MID, RECTIFIER:GRAETZ+DELON:TUNING_CAPS:C3.2_MID, RECTIFIER:GRAETZ+DELON:TUNING_CAPS:C4.2_MID, RECTIFIER:GRAETZ+DELON:TUNING_CAPS:R2.1
RECTIFIER:LDO_IN: RECTIFIER:3V3:C2.1, RECTIFIER:3V3:IC1.1_VDD, RECTIFIER:3V3:IC2.IN, RECTIFIER:3V3:R1.1, RECTIFIER:D1.C, RECTIFIER:D2.C
RECTIFIER:PHASE_SHIFT:OPAMP_IN+: RECTIFIER:PHASE_SHIFT:IC1.3, RECTIFIER:PHASE_SHIFT:R2.2
RECTIFIER:PHASE_SHIFT:OPAMP_IN-: RECTIFIER:PHASE_SHIFT:IC1.4, RECTIFIER:PHASE_SHIFT:R3.2
RECTIFIER:PHASE_SHIFT:OPAMP_OUT: RECTIFIER:PHASE_SHIFT:IC1.1, RECTIFIER:PHASE_SHIFT:R1.1
RECTIFIER:SMOOTHINGCAP_IN: RECTIFIER:GRAETZ+DELON:D1.A, RECTIFIER:GRAETZ+DELON:D3.A, RECTIFIER:GRAETZ+DELON:DELON:C1.1_POS, RECTIFIER:GRAETZ+DELON:TUNING_CAPS:R2.2, RECTIFIER:SMOOTHING_CAP:D8.C
RECTIFIER:ZERO-CROSS_DETECTOR:OPAMP_IN+: RECTIFIER:ZERO-CROSS_DETECTOR:IC1.P$3, RECTIFIER:ZERO-CROSS_DETECTOR:R2.2
RECTIFIER:ZERO-CROSS_DETECTOR:OPAMP_OUT: RECTIFIER:ZERO-CROSS_DETECTOR:IC1.P$1, RECTIFIER:ZERO-CROSS_DETECTOR:R3.1
RECTIFIER:ZERO-CROSS_DETECTOR:ZC_LP_OUT: RECTIFIER:ZERO-CROSS_DETECTOR:C8.2, RECTIFIER:ZERO-CROSS_DETECTOR:D1.C, RECTIFIER:ZERO-CROSS_DETECTOR:R1.2, RECTIFIER:ZERO-CROSS_DETECTOR:R2.1
RN4678_CONNSTAT: BLUETOOTH:IC1.12, STM32L4:IC1.P$4
RN4678_CTS: BLUETOOTH:IC1.17, STM32L4:IC1.P$32
RN4678_RST: BLUETOOTH:IC1.21, STM32L4:IC1.P$20
RN4678_RTS: BLUETOOTH:IC1.15, STM32L4:IC1.P$33
RN4678_RX: BLUETOOTH:IC1.23, STM32L4:IC1.P$31, TP3.P$1
RN4678_TRANSSTAT: BLUETOOTH:IC1.11, STM32L4:IC1.P$3
RN4678_TX: BLUETOOTH:IC1.22, STM32L4:IC1.P$30, TP4.P$1
RN4678_WKUP: BLUETOOTH:IC1.9, STM32L4:IC1.P$41, TP5.P$1
RXCAN: CAN_INFRA:IC1.P$4, STM32L4:IC1.P$45
SDMMC_CLK: SD_CARD:IC3.6, STM32L4:IC1.P$25
SDMMC_CMD: SD_CARD:IC3.5, STM32L4:IC1.P$11
SDMMC_DATA0: SD_CARD:IC3.7, STM32L4:IC1.P$27
SDMMC_DATA1: SD_CARD:IC3.8, STM32L4:IC1.P$28
SDMMC_DATA2: SD_CARD:IC3.3, STM32L4:IC1.P$39
SDMMC_DATA3: SD_CARD:IC3.4, STM32L4:IC1.P$40
SDMMC_DET: SD_CARD:IC1.CARD_DETECT, SD_CARD:IC3.1, STM32L4:IC1.P$26
SD_CARD:CLK_EX: SD_CARD:IC1.CLK, SD_CARD:IC3.11
SD_CARD:CMD_EX: SD_CARD:IC1.CMD, SD_CARD:IC3.12
SD_CARD:DAT0_EX: SD_CARD:IC1.DATA0, SD_CARD:IC3.10
SD_CARD:DAT1_EX: SD_CARD:IC1.DATA1, SD_CARD:IC3.9
SD_CARD:DAT2_EX: SD_CARD:IC1.DATA2, SD_CARD:IC3.14
SD_CARD:DAT3_EX: SD_CARD:IC1.CD/DATA3, SD_CARD:IC3.13
SYS_NRST: CONN1.27, CONN1.28, IC2.I3, STM32L4:C4.2, STM32L4:IC1.P$7
SYS_SWCLK: CONN1.29, CONN1.30, IC2.I1, STM32L4:IC1.P$37
SYS_SWDIO: CONN1.31, CONN1.32, IC2.I4, STM32L4:IC1.P$34
TXCAN: CAN_INFRA:IC1.P$1, STM32L4:IC1.P$46
VDC: ADJUSTABLE_LOAD:INA219:R4.1, ADJUSTABLE_LOAD:INA219:R5.2, CONN1.63, CONN1.64, CONN1.65, CONN1.66, CONN1.67, CONN1.68, RECTIFIER:D2.A, RECTIFIER:SMOOTHING_CAP:C1.+, RECTIFIER:SMOOTHING_CAP:D8.A
ZEROCROSS: CONN1.49, CONN1.50, IC1.I3, RECTIFIER:ZERO-CROSS_DETECTOR:R3.2, STM32L4:IC1.P$10
